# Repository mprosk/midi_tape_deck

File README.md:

# MIDI Tape Deck
MIDI controlled tape deck. Dynamically adjust the pitch of a recording to a specific pitch based on MIDI note data.

This project is built around the Yamaha KX-130 but can likely be adapted to other decks and mechanisms

## Theory of Operation

Cassette tapes are designed to run at a nominal rate of 1.75 inches per second. When the speed of tape playback is changed, the resulting sound will have a change in pitch. The slower the speed, the lower the pitch, and vice versa. By adjusting the speed of tape playback by a specific amount, the pitch of the recording can be changed to a specific note, assuming the nominal pitch of the recording is known.

This project provides the hardware and software for performing such a task.

### Speed Control

In the tape deck used in this project, the tape speed could be adjusted using a 1k potentiometer. The pitch range of the 1k pot was quite limited, meaning that few notes could be reached. Experimentation revealed that the larger the value of the potentiometer, the larger the change in frequency, and thus the more notes that could be tuned to. In addition, the change in pitch as a function of the change of resistance was observed to be linear.

Digital potentiometers are one way of interfacing digital and analog systems. The value of the pot can be changed in software but wired to the tape deck in place of the existing 1k pot. However, digital potentiometers typically have only 128 or 256 "taps" on them, meaning they can only stop at a fairly low number of values between the minimum and maximum values. This is in contrast to the mechanically actuated potentiometer, which can be adjusted continuously along is range.

Due to the low number of taps, a single digital potentiometer would not be able to control the tape deck with enough precision to reach a specific note. In order to mitigate this, two digital potentiometers were ganged together in the circuit shown below.

This configuration results in one of the potentiometers causing a larger change in the overall resistance, while the other produced a larger change, creating a "coarse" setting and a "fine" setting. This configuration allowed for a much larger number of frequencies to be reached, as  instead of 256 discrete points, there were now 256<sup>2</sup> different combinations across the two potentiometers. 

### Transfer Function

The purpose of the potentiometers is to adjust the playback speed of the tape such that the frequency is changed by a target amount. In order to know what values to set the potentiometers to, we must know what the relationship between the potentiometer settings and the change in frequency is in the first place. By understanding this relationship, we can figure out what pot settings we need to obtain the desired change in pitch.

This system has two independent variables--the settings of the coarse and fine potentiometers--and one dependent variable--the change in pitch of the tape. By stepping through a range of combinations of potentiometers settings and recording the resulting pitch shift, we can start to see the relationship develop.

Note that this relationship is only linear when the coarse potentiometer is changed, and is nonlinear when the fine potentiometer is changed. Also note how the coarse potentiometer has a greater impact on the output frequency than the fine potentiometer. 

Once we have captured enough data points, a best fit equation can be calculated for the surface using polynomial regression. This is performed in `eval/eval.py`. This produces a formula that equates the change in output frequency based on the coarse (x) and fine (y) potentiometer settings.

```
freq(x,y) = -1503.0871471 + 12.0767089x + 0.9015391y + 0.0115233xy + 0.003259y^2
```

### Equation Solver

Now that we are able to calculated the change in output frequency for a given combination of coarse and fine settings, we can start to work on the inverse: finding the combination of potentiometer settings that result in the desired change in output frequency.

Solving the equation mathematically for a given frequency is not conducive to an embedded device (or me) so this approach will be a little more brute-force, essentially a recursive guess-and-check.

First, the setting of the fine potentiometer is fixed to 127. A binary search is performed on the setting of the coarse potentiometer, using the equation above to determine what the output frequency will be. Once a coarse settings is found that puts the output close enough to the target value, the same operation is repeated for the fine potentiometer. Essentially the coarse pot is adjust to get the output close, then final adjustment is made using the fine pot.

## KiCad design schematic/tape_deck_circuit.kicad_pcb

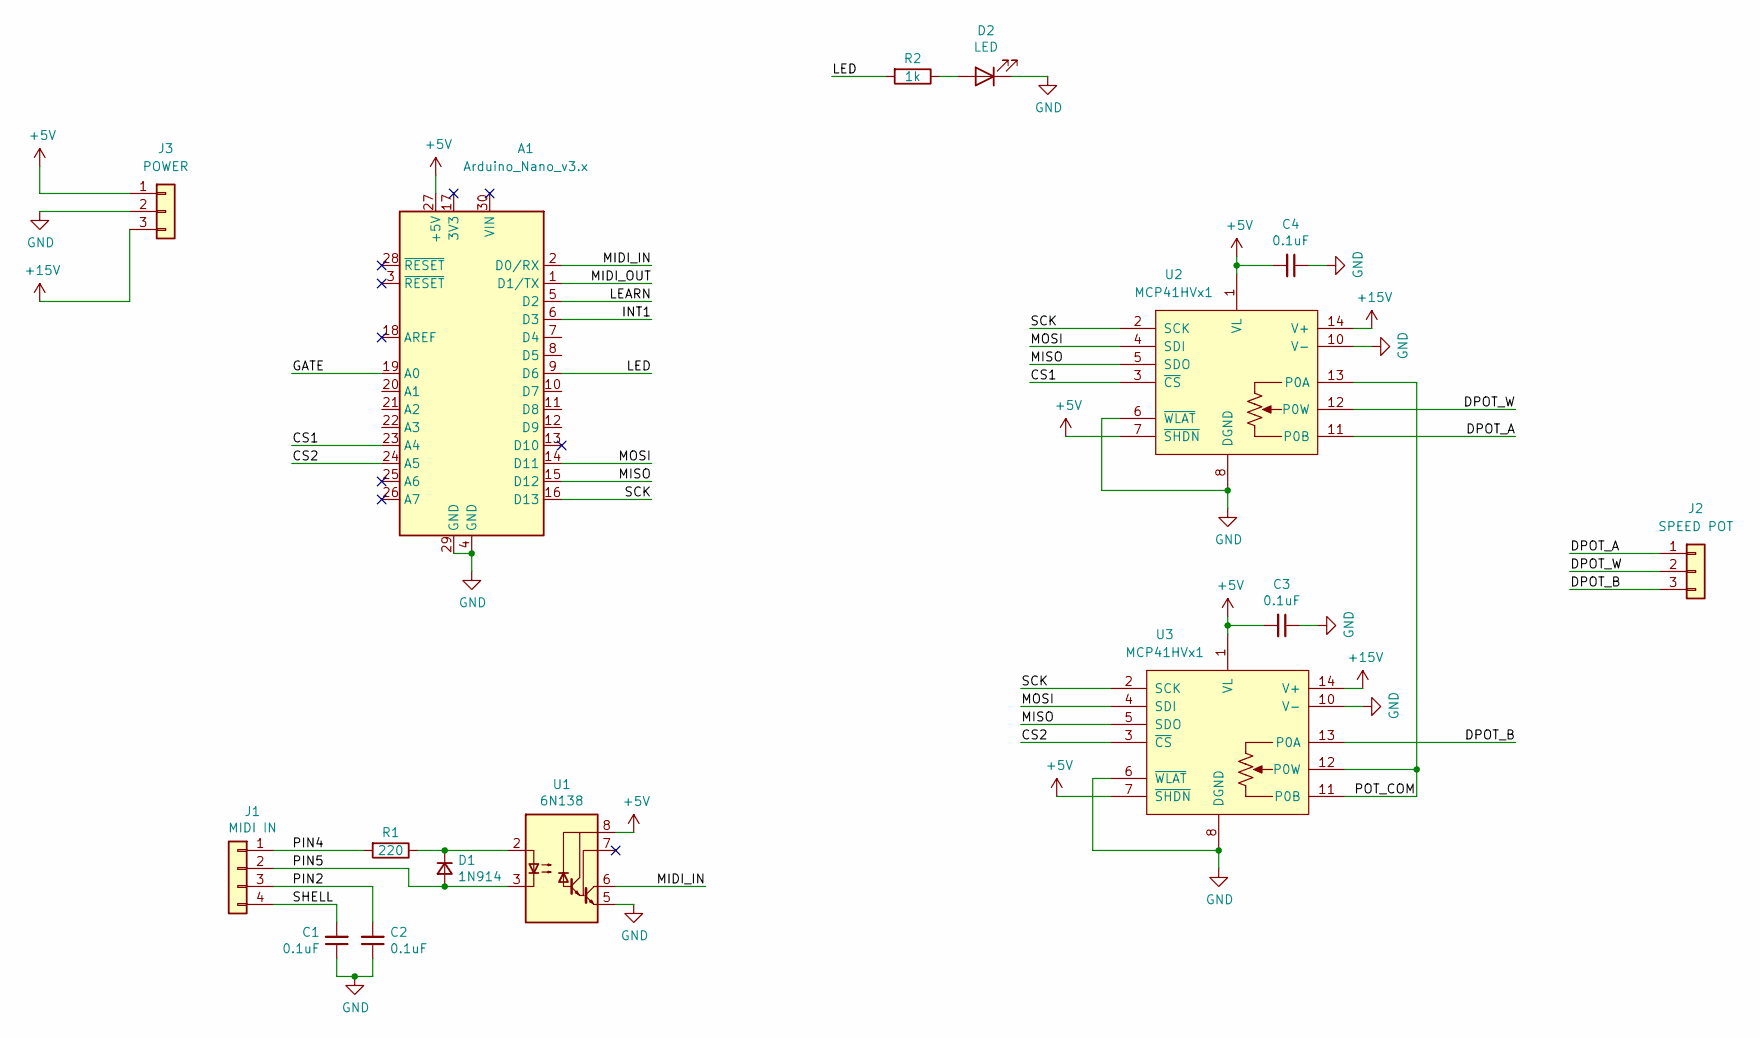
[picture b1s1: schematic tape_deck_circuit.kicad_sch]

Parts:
A1: Arduino_Nano_v3.x; Arduino_Nano
C1, C2, C3, C4: 0.1uF; C_Disc_D3.0mm_W1.6mm_P2.50mm
D1: 1N914; D_DO-35_SOD27_P7.62mm_Horizontal
D2: LED; PinHeader_1x02_P2.54mm_Vertical
J1: MIDI IN; PinHeader_1x04_P2.54mm_Vertical
J2: SPEED POT; PinHeader_1x03_P2.54mm_Vertical
J3: POWER; PinHeader_1x03_P2.54mm_Vertical
R1: 220; R_Axial_DIN0207_L6.3mm_D2.5mm_P10.16mm_Horizontal
R2: 1k; R_Axial_DIN0207_L6.3mm_D2.5mm_P10.16mm_Horizontal
U1: 6N138; DIP-8_W7.62mm_Socket
U2, U3: MCP41HVx1; TSSOP_Breakout

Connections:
+5V: A1.27 (+5V), C3.2, C4.2, J3.1, U1.8 (VCC), U2.1 (VL), U2.7 (~SHDN), U3.1 (VL), U3.7 (~SHDN)
+15V: J3.3, U2.14 (V+), U3.14 (V+)
/CS1: A1.23 (A4), U2.3 (~CS)
/CS2: A1.24 (A5), U3.3 (~CS)
/DPOT_A: J2.1, U2.11 (P0B)
/DPOT_B: J2.3, U3.13 (P0A)
/DPOT_W: J2.2, U2.12 (P0W)
/GATE: A1.19 (A0)
/INT1: A1.6 (D3)
/LEARN: A1.5 (D2)
/LED: A1.9 (D6), R2.2
/MIDI_IN: A1.2 (D0/RX), U1.6 (VO2)
/MIDI_OUT: A1.1 (D1/TX)
/MISO: A1.15 (D12), U2.5 (SDO), U3.5 (SDO)
/MOSI: A1.14 (D11), U2.4 (SDI), U3.4 (SDI)
/PIN2: C2.2, J1.3
/PIN4: J1.1, R1.2
/PIN5: D1.2 (A), J1.2, U1.3 (C2)
/POT_COM: U2.13 (P0A), U3.11 (P0B), U3.12 (P0W)
/SCK: A1.16 (D13), U2.2 (SCK), U3.2 (SCK)
/SHELL: C1.2, J1.4
GND: A1.4 (GND), A1.29 (GND), C1.1, C2.1, C3.1, C4.1, D2.1 (K), J3.2, U1.5 (GND), U2.6 (~WLAT), U2.8 (DGND), U2.9 (NC), U2.10 (V-), U3.6 (~WLAT), U3.8 (DGND), U3.9 (NC), U3.10 (V-)
unnamed: D1.1 (K), R1.1, U1.2 (C1)
unnamed: D2.2 (A), R2.1

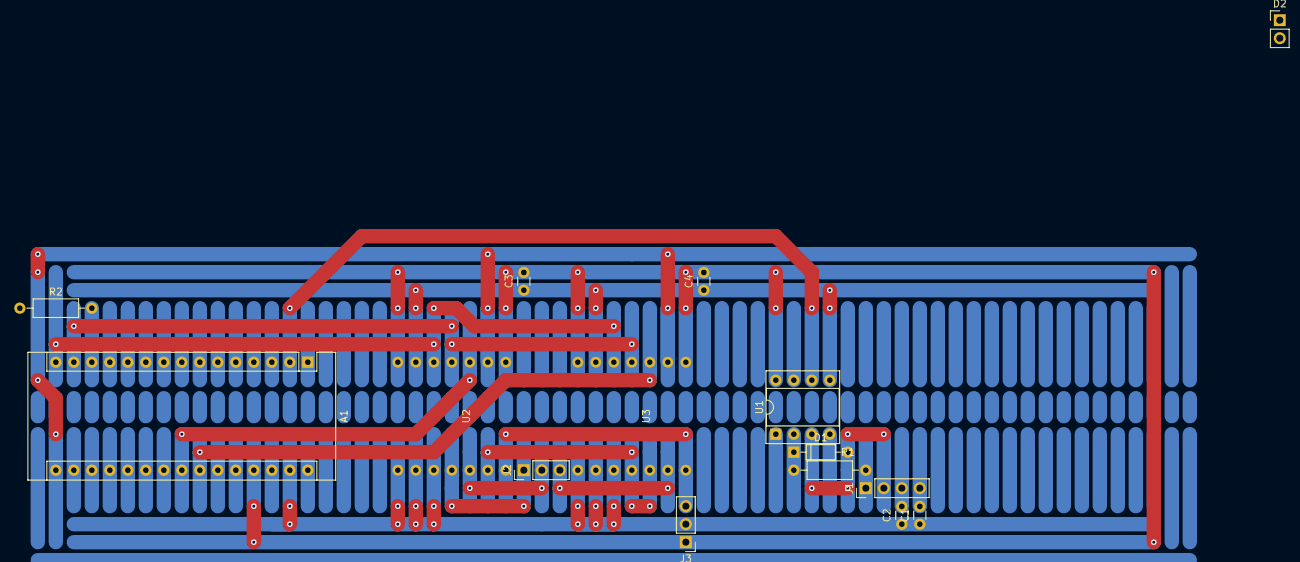
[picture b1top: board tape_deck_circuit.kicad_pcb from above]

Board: 2 copper layers, 15 parts (0 on the bottom side), 20 nets.

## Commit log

2021-08-02 Initial sketch
2021-08-02 Continue sketching out
2021-08-02 Complete basic schematic
2021-08-05 Fix SHDN signal on digipot
2021-08-05 Rename folders. Add test script firmware
2021-08-05 Copy in MIDI module
2021-08-05 Drive chip select when talking to pot
2021-08-05 Allow chip select pin to be set dynamically. Don't use #def in module header
2021-08-10 add results of frequency response test
2021-08-11 prototype remap code
2021-08-16 Continue eval of frequency response
2021-08-16 Update test program to handle two potentiometers
2021-08-24 Add results from experiments with 2 digital pots
2021-08-27 Continue analyzing characteristic curves
2021-08-30 Start working out protoboard layout
2021-08-31 mess with excel some more
2021-08-31 Continue protoboard layout
2021-09-02 Add script for generating 3d plot of frequency curve
2021-09-03 Try to solve for the equation
2021-09-05 Get regression working. Start to sketch solver
2021-09-05 Implement solver in firmware. Create test program
2021-09-05 Improve notes LUT
2021-09-05 Clean up function prototypes
2021-09-07 fix bugs
2021-09-07 fix bugs (#1)
2021-09-07 Mess with solver a bit
2021-09-07 Add MIDI support and clean up comments
2021-09-16 Add support for 5k-5k pot combo
2021-09-16 Fix function misnaming in solve.py
2021-12-16 Add sketch for remote operation of the pots
2021-12-16 Add script for getting frequency measurements from SCPI device
2021-12-16 Take new measurements for 5k-5k pots and update values
2021-12-16 Update 5k-5k equation in main program
2021-12-16 Add image folder
2021-12-16 Get midi working
2021-12-21 Use new frequency change method
2021-12-21 Capture data with new frequency change method. Archive old captures
2021-12-21 Add new equation from new data
2021-12-21 Add incremental adjusts to remote control fw
2021-12-21 Get basic A440 functionality
2022-03-14 Get repitch working with only one 10k pot
2022-03-14 Add the ability to set the nominal pitch value
2022-03-16 Clean up schematic
2022-03-16 More cleanup of schematic files
2022-03-16 Start sketching out synth voice PCB
